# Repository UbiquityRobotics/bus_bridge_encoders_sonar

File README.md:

# bus_bridge_encoders_sonar

The are currently 4 revisions -- `rev_a`, `rev_b`, `rev_c`,
and `rev_d`.  The schematic is available as bus_bridge_encoders_sonar.pdf`
or as `bus_bridge_encoders_sonar.svg` in the appropriate revision
directory.

## Rev. A Issues

* Tie off unused inputs of U7 to 0V or 5V. [x]

* Replace R8, R9, R10, R11, R12, R13 with a 10K ohm SIP package. [x]

* Add protection diodes to the motor outputs.  The 754410 does
  **not** have protection diodes like the L793D did.  [No.  If
  it is an issue, use the L293D instead.]

* Adding a 2x3 pin ISP programming header. [x]

* The U8 TXD (pin 1) and RXD (pin 4) are swapped. [x]

* Replace the R17, R18, R20, R21 voltage dividers with 100K pull-ups. [x]

* Add a 100K pull up U7A pin 1 to protect against U8 not
  being plugged in. [x]

* Combine Encoder and Motor onto a single 2x4 ribbon cable. [x]

* Add an LED that can be blinked. [x]

## Rev. B Issues

* Connected U8 STBY (pin 8) to a processor pin [x]

## Rev. C Docummentation

<Table Border="1">
    <TR>
    </TR><TR>
	<TH>Arduino Name</TH>
	<TH>AVR Port</TH>
	<TH>Function</TH>
    </TR><TR>
	<TD>D0</TD>
	<TD>PD0/RXD</TD>
	<TD>USART Receive</TD>
    </TR><TR>
	<TD>D1</TD>
	<TD>PD0/TXD</TD>
	<TD>USART Transmit</TD.
    </TR><TR>
	<TD>D2</TD>
	<TD>PD3</TD>
	<TD>SONAR0_TRIG</TD>
    </TR><TR>
	<TD>D3</TD>
	<TD>PD3/OC2B</TD>
	<TD>SONAR0_ECHO</TD>
    </TR><TR>
	<TD>D4</TD>
	<TD>PD4</TD>
	<TD>SONAR1_TRIG</TD>
    </TR><TR>
	<TD>D5</TD>
	<TD>PD6/OC0B</TD>
	<TD>SONAR1_ECHO</TD>
    </TR><TR>
	<TD>D6</TD>
	<TD>PD6/OC0A</TD>
	<TD>ENC_EN</TD>
    </TR><TR>cc
	<TD>D7</TD>
        <TD>PD7<TD>
	<TD>1A</TD>
    </TR><TR>
	<TD>D8</TD>
	<TD>PB0<TD>
	<TD>4A</TD>
    </TR><TR>
	<TD>D9</TD>
	<TD>PB1/OC1A</TD>
	<TD>EN34</TD>
    </TR><TR>
	<TD>D10</TD>
	<TD>PB2/OC1B</TD>
	<TD>EN12</TD>
    </TR><TR>
	<TD>D11</TD>
	<TD>PB3/OC2A</TD>
	<TD>3A</TD>
    </TR><TR>
	<TD>D12</TD>m
	<TD>PB4</TD>
	<TD>2A</TD>
    </TR><TR>
	<TD>D13</TD>
	<TD>PB5</TD>
	<TD>LED</TD>
    </TR><TR>
	<TD>A0</TD>
	<TD>PC0</TD>
	<TD>ENC1_A</TD>
    </TR><TR>
	<TD>A1</TD>
	<TD>PC1</TD>
	<TD>ENC1_B</TD>
    </TR><TR>
	<TD>A2</TD>
	<TD>PC2</TD>
	<TD>ENC2_A</TD>
    </TR><TR>
	<TD>A3</TD>
	<TD>PC3</TD>
	<TD>ENC2_B</TD>
    </TR><TR>
	<TD>A4</TD>
	<TD>PC4</TD>
	<TD>CAN_STBY</TD>
    </TR><TR>
	<TD>A5</TD>
	<TD>PC5</TD>
	<TD>-</TD>
    </TR>
</Table>

## Rev. C Issues

* Schematic should label C13 as 1uF. [x]

* Schematic should label R4 as 120_1%. [x]

* Schematic has BGND and BPWR swapped on root diagram. [x]

* Make sure regulator input capacitors can take 30V.  Probably switch
  over to aluminum electrolytic capacitor. [x]

* Move ISP connector up to make more room for Atmel-ICE connector. [x]

* Between Dual Slot Encoder (Rev. D) and Rev. C of this
  board, pins 4 and 5 are swapped as are pins 6 and 7.
  [change dual slot encoders instead]
  See below:

<BlockQuote>
<Pre>
     BBES-C       DSE-D
    ===========================
     MOTOR_A   1  MOTOR_A
     MOTOR_A   2  MOTOR_A
     LOG_5V    3  LPWR (=5V)
     LGND      4  QUAD_A
     QUAD_A    5  LGND (not really used)
     QUAD_B    6  LED_EN
     LED_EN    7  QUAD_B
     LED_5V    8  BPWR
     MOTOR_B   9  MOTOR_B
     MOTOR_B  10  MOTOR_B
</Pre>
</BlockQuote>

## Rev. D Issues

* The vertical resistors are hard to solder.  Think about switching

* Update schematic to specifiy electrolytic capacistors for input
  voltage regulators.

* The C5 is too close to the mounting hole.

* Think about adding an LED jumper block.

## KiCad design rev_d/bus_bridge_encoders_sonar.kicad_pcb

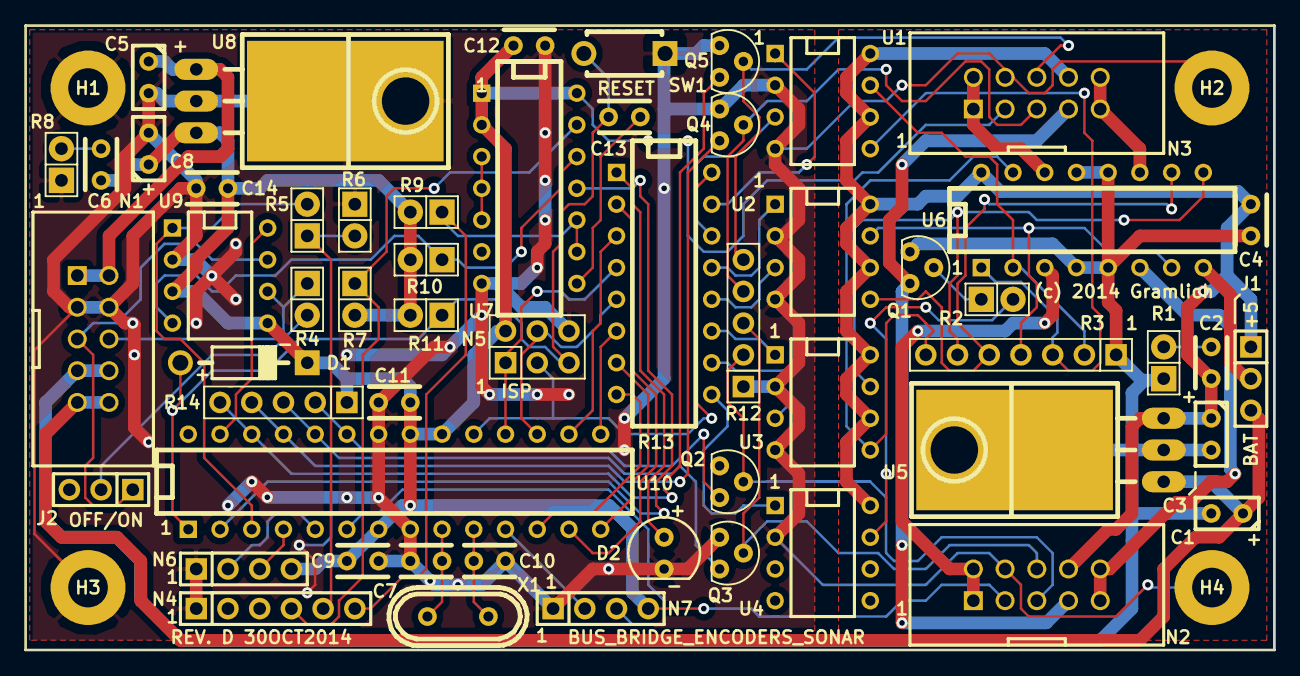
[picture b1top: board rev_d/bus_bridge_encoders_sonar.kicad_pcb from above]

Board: 2 copper layers, 100.0 x 50.0 mm, 61 parts (1 on the bottom side), 65 nets.

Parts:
C1, C3, C5, C8: 22uF; Capacitor3MMDiscRM2.5
C2, C4, C6, C9, C11, C12, C14: .1uF; Capacitor4x3RM2-5_RevB
C7, C10: 18pF; Capacitor4x3RM2-5_RevB
C13: 1uF; Capacitor4x3RM2-5_RevB
D1: SD101C-TR; Diode_DO-41_SOD81_Horizontal_RM10
D2: LED; T1_LED
G1: OSHW_LOGO; OSHW_LOGO_300mil
H1, H2, H3, H4: 3MM_HOLE; MountingHole_3mm
J1: POWER_SELECT; Pin_Header_Straight_1x03
J2: TERMINATE_JUMPER; Pin_Header_Straight_1x03
N1: BUS_SLAVE_HEADER; Pin_Header_Straight_2x05_Shrouded
N2, N3: MOTOR_ENCODER_CONN_2X5; Pin_Header_Straight_2x05_Shrouded
N4: FTDI_HEADER; Pin_Header_Straight_1x06
N5: AVR_ISP_HEADER; Pin_Header_Straight_2x03
N6, N7: HC_SR04_CONNECTOR; Pin_Header_Straight_1x04
Q1, Q2, Q3, Q4, Q5: PN2222; TO92_123
R1, R8: .47; Pin_Header_Straight_1x02
R2: 220; Pin_Header_Straight_1x02
R3: 10Kx6; Pin_Header_Straight_1x07
R4: 120; Pin_Header_Straight_1x02
R5: 22K; Pin_Header_Straight_1x02
R6: 33K; Pin_Header_Straight_1x02
R7, R9, R10: 100K; Pin_Header_Straight_1x02
R11: 10K; Pin_Header_Straight_1x02
R12: 4K7x4; Pin_Header_Straight_1x05
R13: 470_DIP16; DIP-16__300
R14: 3K3x4; Pin_Header_Straight_1x05
SW1: MJTP1243; Button_6.5MM
U1, U2, U3, U4: LTV-826; DIP-8__300
U5, U8: LM2940; TO-220_Neutral123_Horizontal_LargePads
U6: 754410; DIP-16__300
U7: 74HCT08; DIP-14__300
U9: MCP2562; DIP-8__300
U10: ATMEGA328_DIP28; DIP-28__300
X1: 16MHz; Crystal_HC49-U_Vertical

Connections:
+5V: C6.1, C8.1, C9.1, C11.1, C12.1, C14.1, D1.-, N2.3, N3.3, N5.2, N6.4, N7.4, R7.2, R9.2, R10.2, R11.2, R14.1, U7.1, U7.2, U7.14, U8.3, U9.3, U9.5, U10.7, U10.20, U10.21
/Logic/1A: R13.15, U1.1
/Logic/2A: R13.13, U2.1
/Logic/3A: R13.12, U2.3
/Logic/4A: R13.10, U3.3
/Logic/A0: Q2.3, R14.2, U10.23
/Logic/A1: Q3.3, R14.3, U10.24
/Logic/A2: Q4.3, R14.4, U10.25
/Logic/A3: Q5.3, R14.5, U10.26
/Logic/A4: U9.8, U10.27
/Logic/CANH: J2.1, N1.5, U9.7
/Logic/CANL: N1.6, R4.1, U9.6
/Logic/D2: N6.3, U10.4
/Logic/D3: N6.2, U10.5
/Logic/D4: N7.3, U10.6
/Logic/D5: N7.2, U10.11
/Logic/D6: R13.8, U10.12
/Logic/D7: R13.2, U10.13
/Logic/D8: R13.7, U10.14
/Logic/D9: R13.6, U10.15
/Logic/D10: R13.3, U10.16
/Logic/D11: N5.4, R13.5, U10.17
/Logic/D12: N5.1, R13.4, U10.18
/Logic/D13: N5.3, R13.16, U10.19
/Logic/EN12: R13.14, U1.3
/Logic/EN34: R13.11, U3.1
/Logic/ENC1_A: N2.5, Q2.2, R12.2
/Logic/ENC1_B: N2.6, Q3.2, R12.3
/Logic/ENC2_A: N3.5, Q4.2, R12.4
/Logic/ENC2_B: N3.6, Q5.2, R12.5
/Logic/ENC_EN: R13.9, U4.1
/Logic/LPWR: C5.1, N1.1, N1.2, U8.1
/Logic/RXD: U7.11, U10.2
/Logic/TXD: R5.2, U9.1, U10.3
/Logic/~RESET: C13.2, D1.+, N5.5, R11.1, SW1.2, U10.1
/Power/BGND: C1.2, C3.2, C4.2, N1.7, N1.8, Q1.1, R1.1, R3.1, U5.2, U6.4, U6.5, U6.12, U6.13
/Power/BPWR: C1.1, J1.3, N1.9, N1.10, U5.1
/Power/LED_5V: C2.1, C3.1, C4.1, J1.1, N2.8, N3.8, U1.6, U1.8, U2.6, U2.8, U3.6, U3.8, U4.8, U5.3, U6.16
/Power/LED_EN: N2.7, N3.7, Q1.3
/Power/MOTOR1_A: N2.1, N2.2, U6.3
/Power/MOTOR1_B: N2.9, N2.10, U6.6
/Power/MOTOR2_A: N3.9, N3.10, U6.11
/Power/MOTOR2_B: N3.1, N3.2, U6.14
/Power/MOTOR_POWER: J1.2, U6.8
GND: C5.2, C7.2, C8.2, C9.2, C10.2, C11.2, C12.2, C14.2, D2.-, H1.1, H2.1, H3.1, H4.1, N1.3, N1.4, N2.4, N3.4, N4.1, N5.6, N6.1, N7.1, Q2.1, Q3.1, Q4.1, Q5.1, R6.1, R8.1, R12.1, SW1.1, U1.2, U1.4, U2.2, U2.4, U3.2, U3.4, U4.2, U7.7, U8.2, U9.2, U10.8, U10.22
unnamed: C2.2, R1.2
unnamed: C6.2, R8.2
unnamed: C7.1, U10.9, X1.1
unnamed: C10.1, U10.10, X1.2
unnamed: C13.1, U7.8
unnamed: D2.+, R13.1
unnamed: J2.2, R4.2
unnamed: N4.4, R7.1, U7.13
unnamed: N4.5, R5.1, R6.2
unnamed: N4.6, R9.1, U7.9, U7.10
unnamed: Q1.2, R2.1
unnamed: R2.2, U4.7
unnamed: R3.2, U1.7, U6.2
unnamed: R3.3, U1.5, U6.1
unnamed: R3.4, U2.7, U6.7
unnamed: R3.5, U2.5, U6.10
unnamed: R3.6, U3.7, U6.9
unnamed: R3.7, U3.5, U6.15
unnamed: R10.1, U7.12, U9.4
unnamed: U7.3, U7.4, U7.5

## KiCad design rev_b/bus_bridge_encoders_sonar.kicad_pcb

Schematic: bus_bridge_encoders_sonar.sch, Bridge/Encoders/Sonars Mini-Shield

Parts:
C1, C3, C6, C9: 22uF; Capacitor4x3RM2-5_RevB
C2, C4, C8, C10, C11, C12, C13, C14: .1uF; Capacitor3MMDiscRM2.5
C5, C7: 18pF; Capacitor3MMDiscRM2.5
D1: SD101C-TR; Diode_DO-41_SOD81_Horizontal_RM10
D2: LED; T1_LED
G1: OSHW_LOGO; OSHW_LOGO_300mil
H1, H2, H3, H4: 3MM_HOLE; MountingHole_3mm
J1: POWER_SELECT; Pin_Header_Straight_1x03
J2: TERMINATE_JUMPER; Pin_Header_Straight_1x03
N1: BUS_SLAVE_HEADER; Pin_Header_Straight_2x05_Shrouded
N2: FTDI_HEADER; Pin_Header_Straight_1x06
N3: AVR_ISP_HEADER; Pin_Header_Straight_2x03
N5, N6: MOTOR_ENCODER_CONN; Pin_Header_Straight_2x04_Shrouded
N7, N8: HC_SR04_CONNECTOR; Pin_Header_Straight_1x04
R1, R14, R19: .47; Resistor_Horizontal_400
R2: 470_DIP16; DIP-16__300
R8: 10Kx6; Pin_Header_Straight_1x07
R15: 22K; Resistor_Horizontal_400
R16: 33K; Resistor_Horizontal_400
R17, R18, R20: 100K; Resistor_Horizontal_400
R22: 10K; Resistor_Horizontal_400
SW1: MJTP1243; Button_6.5MM
U1, U6: LM2940; TO-220_Neutral123_Horizontal_LargePads
U2, U3, U4: LTV-826; DIP-8__300
U5: 754410; DIP-16__300
U7: 74HCT08; DIP-14__300
U8: MCP2562; DIP-8__300
U9: ATMEGA328_DIP28; DIP-28__300
X1: 16MHz; Crystal_HC49-U_Vertical

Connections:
/A0: N5.1, U9.23 (PC0/ADC0)
/A1: N5.7, U9.24 (PC1/ADC1)
/BGND: C1.2, C3.2, C4.2, N1.7 (BGND1), N1.8 (BGND2), R1.1, R8.1, U1.2, U5.4 (GND), U5.5 (GND), U5.12 (GND), U5.13 (GND)
/BPWR: C1.1, J1.1 (VIN1), N1.9 (BPWR1), N1.10 (BPWR2), U1.1 (VIN)
/D2: N6.1, U9.4 (PD2/INT0)
/D3: N8.2 (ECHO), U9.5 (PD3/OC2B/INT1)
/D4: N8.3 (TRIG), U9.6 (PD4/XCK/T0)
/D5: N7.3 (TRIG), U9.11 (PD6/OC0B/T11)
/D6: N7.2 (ECHO), U9.12 (PD6/OC0A/AIN0)
/D7: N6.7, U9.13 (PD7/AIN1)
/D8: R2.6, U9.14 (PB0/CLKO/ICP1)
/D9: R2.5, U9.15 (PB1/OC1A)
/D10: R2.1, U9.16 (PB2/SS/OC1B)
/D11: N3.4, R2.3, U9.17 (PB3/MOSI/OC2A)
/D12: N3.1, R2.2, U9.18 (PB4/MISO)
/D13: N3.3, R2.4, U9.19 (PB5/SCK)
/LPWR: C6.1, N1.1 (LPWR1), N1.2 (LPWR2), U6.1 (VIN)
/M1+: N6.3, N6.4, U5.3 (1Y)
/M1-: N6.5, N6.6, U5.6 (2Y)
/M2+: N5.3, N5.4, U5.11 (3Y)
/M2-: N5.5, N5.6, U5.14 (4Y)
/M5V: C2.1, C3.1, C4.1, J1.3 (VIN2), U1.3 (VOUT), U2.6, U2.8, U3.6, U3.8, U4.6, U4.8, U5.16 (VCC1)
/MOTOR_POWER: J1.2 (VOUT), U5.8 (VCC2)
/RXD: U7.3, U9.2 (PD0/RXD)
/TXD: R15.2, U8.1 (TXD), U9.3 (PD1/TXD)
/~RESET: C10.2, D1.+, N3.5, R22.1, SW1.2, U9.1 (PC6/~RESET)
GND: C5.2, C6.2, C7.2, C9.2, C11.2, C12.2, C13.2, C14.2, D2.-, H1.1, H2.1, H3.1, H4.1, N1.3 (LGND1), N1.4 (LGND2), N2.1 (GND), N3.6, N5.2, N6.2, N7.1 (GND), N8.1 (GND), R14.1, R16.1, SW1.1, U2.2, U2.4, U3.2, U3.4, U4.2, U4.4, U6.2, U7.7 (GND), U8.2 (VSS), U8.8 (STBY), U9.8 (GND), U9.22 (GND)
unnamed: C2.2, R1.2
unnamed: C5.1, U9.9 (PB6/XTAL1), X1.1
unnamed: C7.1, U9.10 (PB7/XTAL2), X1.2
unnamed: C8.2, R14.2
unnamed: C10.1, U7.6
unnamed: D2.+, R2.7
unnamed: J2.1 (ON), N1.6 (CANL), U8.6 (CANL)
unnamed: J2.2 (COM), R19.2
unnamed: N1.5 (CANH), R19.1, U8.7 (CANH)
unnamed: N2.4 (TXD), R17.1, U7.2
unnamed: N2.5 (RXD), R15.1, R16.2
unnamed: N2.6 (~RTS), R20.1, U7.5
unnamed: R2.10, U9.28 (PC5/ADC5/SCL)
unnamed: R2.11, U4.3
unnamed: R2.12, U4.1
unnamed: R2.13, U3.3
unnamed: R2.14, U3.1
unnamed: R2.15, U2.3
unnamed: R2.16, U2.1
unnamed: R8.2, U4.5, U5.15 (4A)
unnamed: R8.3, U4.7, U5.9 (EN34)
unnamed: R8.4, U3.5, U5.10 (3A)
unnamed: R8.5, U3.7, U5.7 (2A)
unnamed: R8.6, U2.5, U5.1 (EN12)
unnamed: R8.7, U2.7, U5.2 (1A)
unnamed: R18.1, U7.1, U8.4 (RXD)
unnamed: U7.9, U7.10, U7.11
VCC: C8.1, C9.1, C11.1, C12.1, C13.1, C14.1, D1.-, N3.2, N5.8, N6.8, N7.4 (5V), N8.4 (5V), R17.2, R18.2, R20.2, R22.2, U6.3 (VOUT), U7.4, U7.12, U7.13, U7.14 (VCC), U8.3 (VDD), U8.5 (VIO), U9.7 (VCC), U9.20 (AVCC)

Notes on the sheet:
Electrically Isolated
Electrically Isolated
Filter Capacitors
Reset Circuitry
Programmer

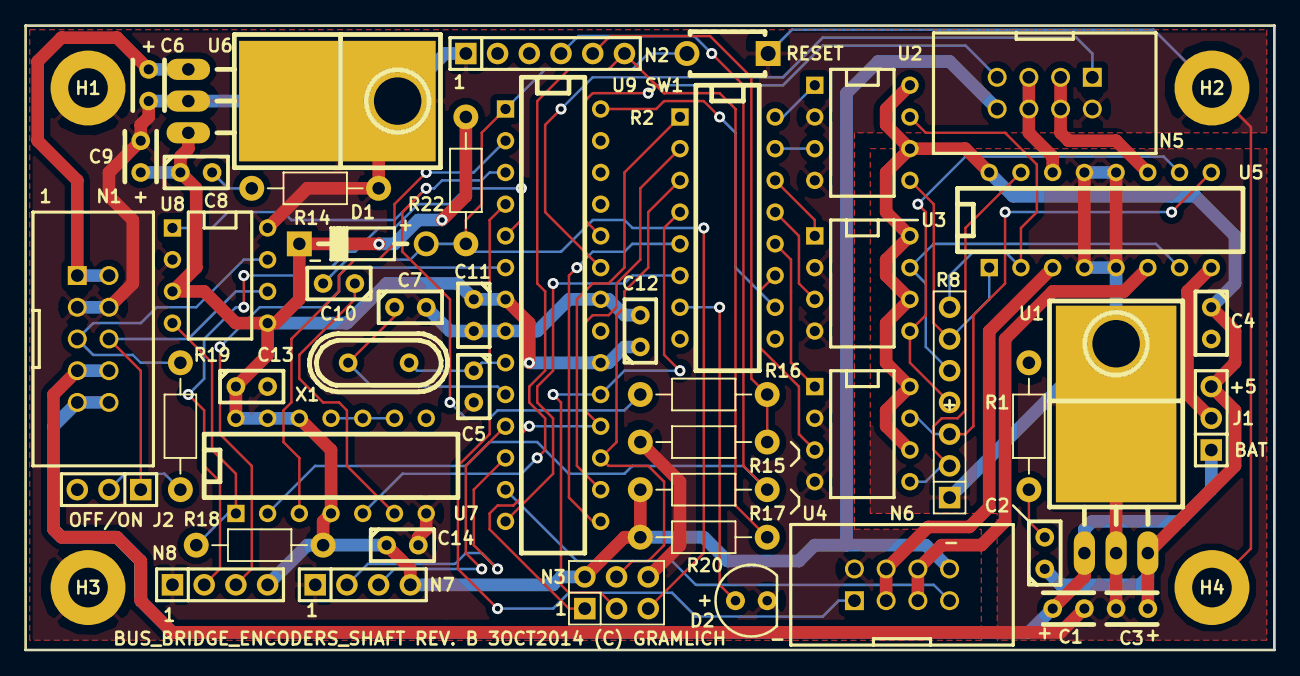
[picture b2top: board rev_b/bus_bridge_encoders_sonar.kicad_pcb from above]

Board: 2 copper layers, 100.0 x 50.0 mm, 52 parts (1 on the bottom side), 55 nets.

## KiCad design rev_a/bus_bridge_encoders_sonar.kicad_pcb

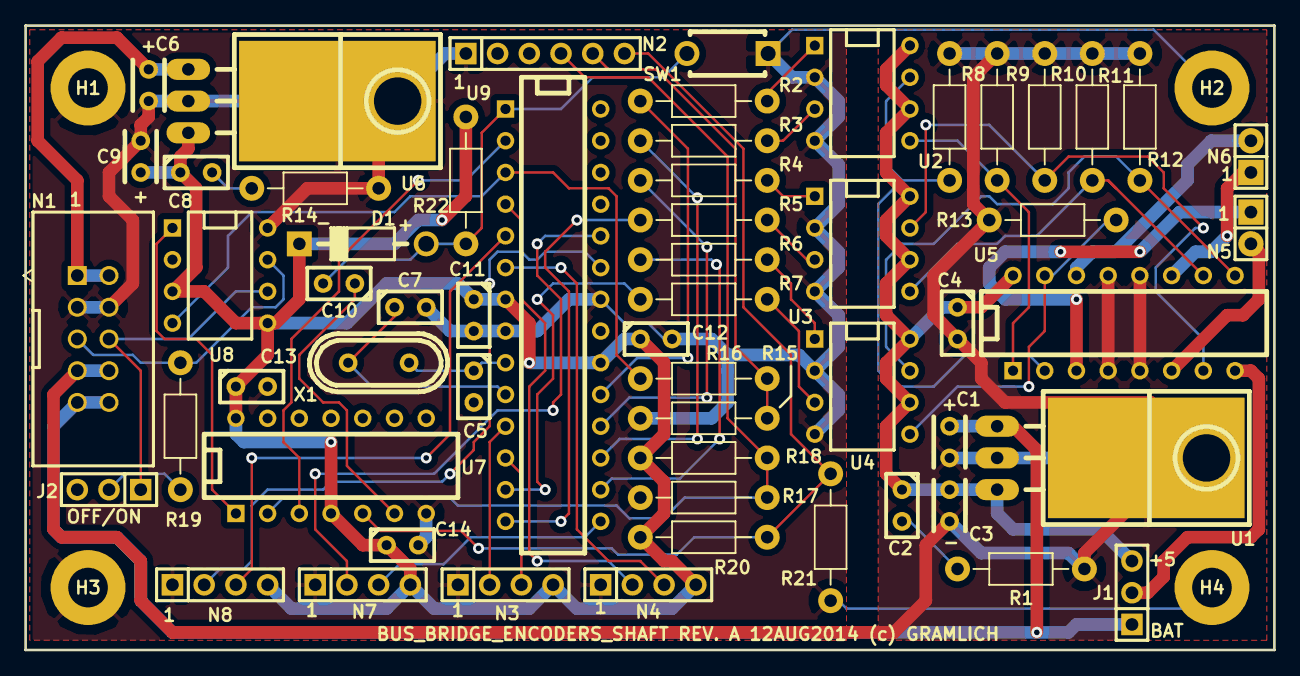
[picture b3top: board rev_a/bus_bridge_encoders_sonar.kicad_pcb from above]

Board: 2 copper layers, 100.0 x 50.0 mm, 63 parts (1 on the bottom side), 52 nets.

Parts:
C1, C3, C6, C9: 22uF; Capacitor4x3RM2-5_RevB
C2, C4, C8, C10, C11, C12, C13, C14: .1uF; Capacitor3MMDiscRM2.5
C5, C7: 18pF; Capacitor3MMDiscRM2.5
D1: SD101C-TR; Diode_DO-41_SOD81_Horizontal_RM10
G1: OSHW_LOGO; OSHW_LOGO_400mil
H1, H2, H3, H4: 3MM_HOLE; MountingHole_3mm
J1: POWER_SELECT; Pin_Header_Straight_1x03
J2: TERMINATE_JUMPER; Pin_Header_Straight_1x03
N1: BUS_SLAVE_HEADER; Pin_Header_Straight_2x05_Shrouded
N2: FTDI_HEADER; Pin_Header_Straight_1x06
N3, N4: ENCODER_CONNECTOR; Pin_Header_Straight_1x04
N5, N6: MOTOR_CONNECTOR; Pin_Header_Straight_1x02
N7, N8: HC_SR04_CONNECTOR; Pin_Header_Straight_1x04
R1, R14, R19: .47; Resistor_Horizontal_400
R2, R3, R4, R5, R6, R7: 470; Resistor_Horizontal_400
R8, R9, R10, R11, R12, R13, R22: 10K; Resistor_Horizontal_400
R15, R17, R20: 22K; Resistor_Horizontal_400
R16, R18, R21: 33K; Resistor_Horizontal_400
SW1: MJTP1243; Button_6.5MM
U1, U6: LM2940; TO-220_Neutral123_Horizontal_LargePads
U2, U3, U4: LTV-826; DIP-8__300
U5: 754410; DIP-16__300
U7: 74HCT08; DIP-14__300
U8: MCP2562; DIP-8__300
U9: ATMEGA328_DIP28; DIP-28__300
X1: CRYSTAL; Crystal_HC49-U_Vertical

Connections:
+5V: C8.1, C9.1, C11.1, C12.1, C13.1, C14.1, D1.-, N3.4, N4.4, N7.4, N8.4, R17.2, R20.2, R22.2, U6.3, U7.4, U7.14, U8.3, U8.5, U9.7, U9.20
/A0: N8.2, U9.23
/A1: N7.2, U9.24
/BGND: C1.2, C3.2, C4.2, N1.7, N1.8, R1.1, R8.1, R9.1, R10.1, R11.1, R12.1, R13.1, U1.2, U5.4, U5.5, U5.12, U5.13
/BPWR: C1.1, J1.1, N1.9, N1.10, U1.1
/D2: N4.2, U9.4
/D3: N8.3, U9.5
/D4: N4.3, U9.6
/D5: N3.2, U9.11
/D6: N3.3, U9.12
/D7: R7.1, U9.13
/D8: R5.1, U9.14
/D9: N7.3, U9.15
/D10: R6.1, U9.16
/D11: R3.1, U9.17
/D12: R4.1, U9.18
/D13: R2.1, U9.19
/LPWR: C6.1, N1.1, N1.2, U6.1
/M1+: N5.1, U5.3
/M1-: N5.2, U5.6
/M2+: N6.1, U5.11
/M2-: N6.2, U5.14
/M5V: C2.1, C3.1, C4.1, J1.3, U1.3, U2.6, U2.8, U3.6, U3.8, U4.6, U4.8, U5.16
/MOTOR_POWER: J1.2, U5.8
/RXD: U7.3, U9.2
/TXD: R15.2, U8.4, U9.3
/~RESET: C10.2, D1.+, R22.1, SW1.2, U9.1
GND: C5.2, C6.2, C7.2, C9.2, C11.2, C12.2, C13.2, C14.2, H1.1, H2.1, H3.1, H4.1, N1.3, N1.4, N2.1, N3.1, N4.1, N7.1, N8.1, R14.1, R16.1, R18.1, R21.1, SW1.1, U2.2, U2.4, U3.2, U3.4, U4.2, U4.4, U6.2, U7.7, U8.2, U8.8, U9.8, U9.22
unnamed: C2.2, R1.2
unnamed: C5.1, U9.9, X1.1
unnamed: C7.1, U9.10, X1.2
unnamed: C8.2, R14.2
unnamed: C10.1, U7.6
unnamed: J2.1, N1.6, U8.6
unnamed: J2.2, R19.2
unnamed: N1.5, R19.1, U8.7
unnamed: N2.4, R17.1, R18.2, U7.2
unnamed: N2.5, R15.1, R16.2
unnamed: N2.6, R20.1, R21.2, U7.5
unnamed: R2.2, U2.1
unnamed: R3.2, U2.3
unnamed: R4.2, U3.1
unnamed: R5.2, U3.3
unnamed: R6.2, U4.1
unnamed: R7.2, U4.3
unnamed: R8.2, U2.7, U5.2
unnamed: R9.2, U2.5, U5.1
unnamed: R10.2, U3.7, U5.7
unnamed: R11.2, U3.5, U5.10
unnamed: R12.2, U4.7, U5.9
unnamed: R13.2, U4.5, U5.15
unnamed: U7.1, U8.1

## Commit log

2014-08-12 Drew schematic for bus_bridge_encoders_sonar.
2014-08-13 Finished Rev. A board layout.
2014-08-18 Added silkscreen outline.
2014-08-18 CRYSTAL=>16MHz
2014-10-02 Updated README.md .
2014-10-02 Switched over to project local fp-lib-table.
2014-10-02 Cloned Rev. A to Rev. B.
2014-10-03 Did first cut of revision B.
2014-10-11 Rev. B is done.
2014-10-11 Cloned Rev. C from Rev. B.
2014-10-21 Forgot to commit Rev. C. Also changed vertical resistors to from pin_header to Resistor_Vertical__100 footprint.
2014-10-30 Regenerated schematics for Rev. C
2014-10-30 Cloned Rev. C into Rev. D.
2014-10-30 Rev. D appears to be ready.
2014-11-16 Added arduino build code.
2014-12-06 Removed some ugliness from schematic.
2014-12-10 Receiving data from bus.
2014-12-10 Got two way bus communication going.
2014-12-12 Got input interrupts working.
2014-12-12 Upgrade to the MB7 version of the bus code.
2014-12-12 maker_bus => bus
2014-12-13 Got basic bus protocol working again.
2014-12-16 Got input mode using Bus::frame_get() in poll mode.
2014-12-16 Got the interrupt test working.
2014-12-16 Worked on code to get it working again.
2014-12-16 Deleted some old commented out code.
2014-12-17 Did first rework of sender side refactoring.
2014-12-17 more Refactoring.
2014-12-18 Have configurator talking over the bus.
2014-12-20 Talking to bus using AVR_UART1
2014-12-21 Got primative UART0 kludged together.
2014-12-21 Removed all occurrances of Serial.
2014-12-21 More UART clean-up.
2014-12-21 Got ECHO_TEST working again.
2014-12-22 Minor changes to Bus.h
2014-12-22 Redid interrupt handlers (not tested.)
2014-12-22 Got interrupts to start working.
2014-12-22 Added some documentation; removed some dead code.
2014-12-22 Got echo test working with interrupts.
2014-12-23 Got command test working with interrupts.
2014-12-23 Got led set/get working over bus on actual bus_bridge_encoders_sonar board.
2014-12-27 Got more register support implemented.
2014-12-27 Got encoders integrated in.
2015-01-01 Got bus protocol working better.
2015-02-13 Split 22uF Capacitors into Aluminum and Tantalum.
2015-03-05 Minor tweak.
2015-03-06 Switched over to Ubiquity core in Arduino.
2015-03-07 Some changes to .xml caused changes to ..._Local.cpp/h.
2015-03-08 Improved .gitignore to ignore .srv files and generate client/server .py files.
2015-03-09 Added Defualt_Address to .xml file.
2015-03-11 Continuing PID refactor.
2015-03-11 Converting to Motor_Encoder Class.
2015-03-11 Minor changes.
2015-03-11 Removed some initial edits.
2015-04-24 Started working on dynamic reconfigure.
2015-05-31 Ignore cfg directory. Add Bus_Bridge_Encoders_Sonar.h

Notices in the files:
rev_d/bus_bridge_encoders_sonar.kicad_pcb:
(c) 2014 Gramlich
